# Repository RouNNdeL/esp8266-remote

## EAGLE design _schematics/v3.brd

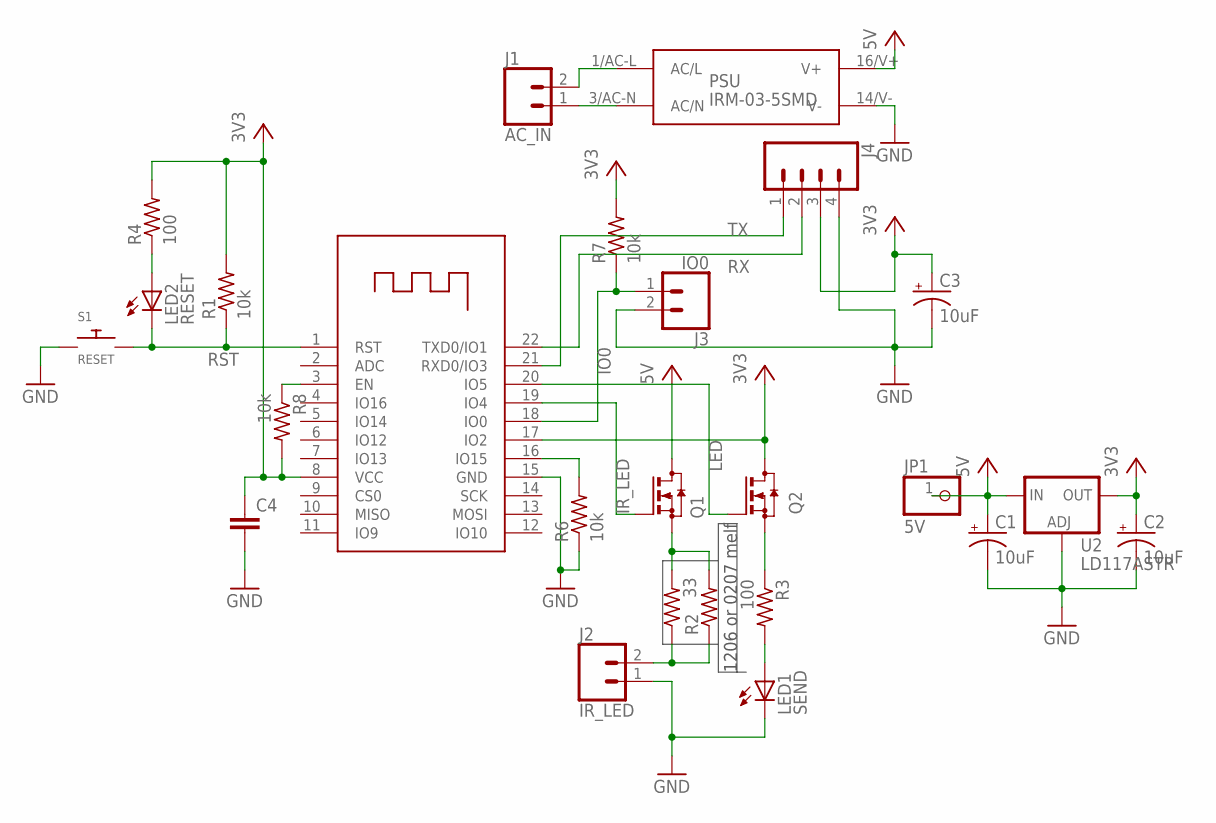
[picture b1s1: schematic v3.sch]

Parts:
C1, C2, C3: 10uF; 153CLV-0405
C4: C-EUC0805; C0805
J1: AC_IN; 1X2_5MM_SCREW
J2: IR_LED; 1X2_5MM_SCREW
J3: IO0; 1X02
J4: CONN_04; 1X04
JP1: 5V; 1X01
LED1: SEND; SML0805
LED2: RESET; SML0805
PSU: IRM-03-5SMD; IRM-03-5S
Q1, Q2: N-MOSFET-SOT23; SOT23
R1, R6, R7, R8: 10k; R0603
R2: 33; MINI_MELF-0207R
R3, R4: 100; R0805
R5: 33; R1206
S1: RESET; B3F-1000
U1: ESP-12F
U2: LD117ASTR; SOT223

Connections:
3V3: C2.+, C3.+, C4.1, J4.3, Q2.3 (D), R1.2, R4.2, R7.2, R8.2, U1.8 (VCC), U1.17 (IO2), U2.4 (OUT)
5V: C1.+, JP1.1, PSU.16/V+ (V+), Q1.3 (D), U2.3 (IN)
AC/L: J1.2, PSU.1/AC-L (AC/L)
AC/N: J1.1, PSU.3/AC-N (AC/N)
EN: R8.1, U1.3 (EN)
GND: C1.-, C2.-, C3.-, C4.2, J2.1, J3.2, J4.4, LED1.C, PSU.14/V- (V-), R6.1, S1.1, S1.2, U1.15 (GND), U2.1 (ADJ)
IO0: J3.1, R7.1, U1.18 (IO0)
IR_LED: Q1.1 (G), U1.19 (IO4)
LED: Q2.1 (G), U1.20 (IO5)
unnamed: LED2.A, R4.1
unnamed: LED1.A, R3.2
unnamed: R6.2, U1.16 (IO15)
unnamed: Q2.2 (S), R3.1
unnamed: Q1.2 (S), R2.2, R5.2
unnamed: J2.2, R2.1, R5.1
RST: LED2.C, R1.1, S1.3, S1.4, U1.1 (RST)
RX: J4.2, U1.22 (TXD0/IO1)
TX: J4.1, U1.21 (RXD0/IO3)

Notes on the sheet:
1206 or 0207 melf

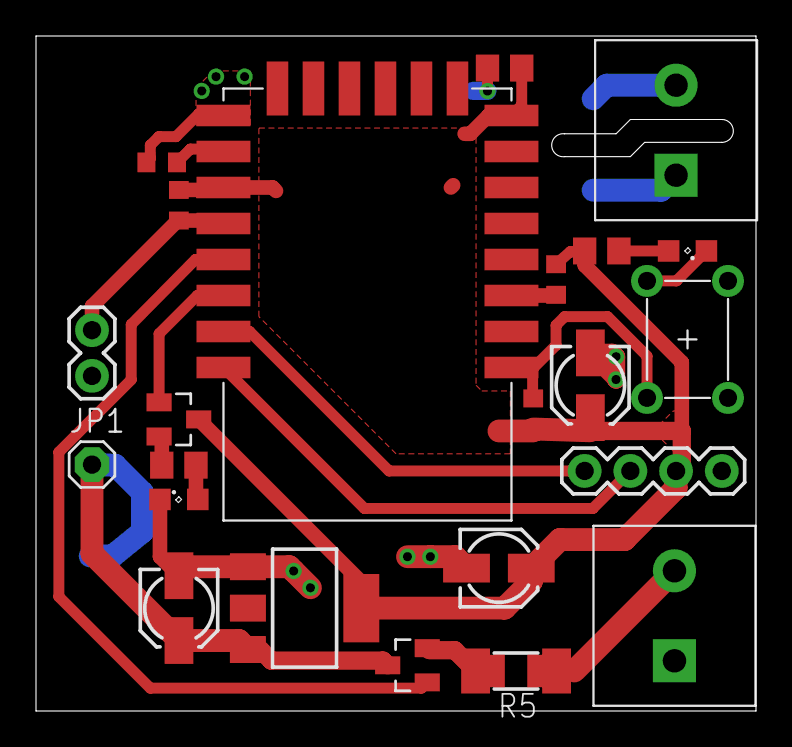
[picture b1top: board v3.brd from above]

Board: 2 copper layers, 40.0 x 37.5 mm, 25 parts (1 on the bottom side), 18 nets.

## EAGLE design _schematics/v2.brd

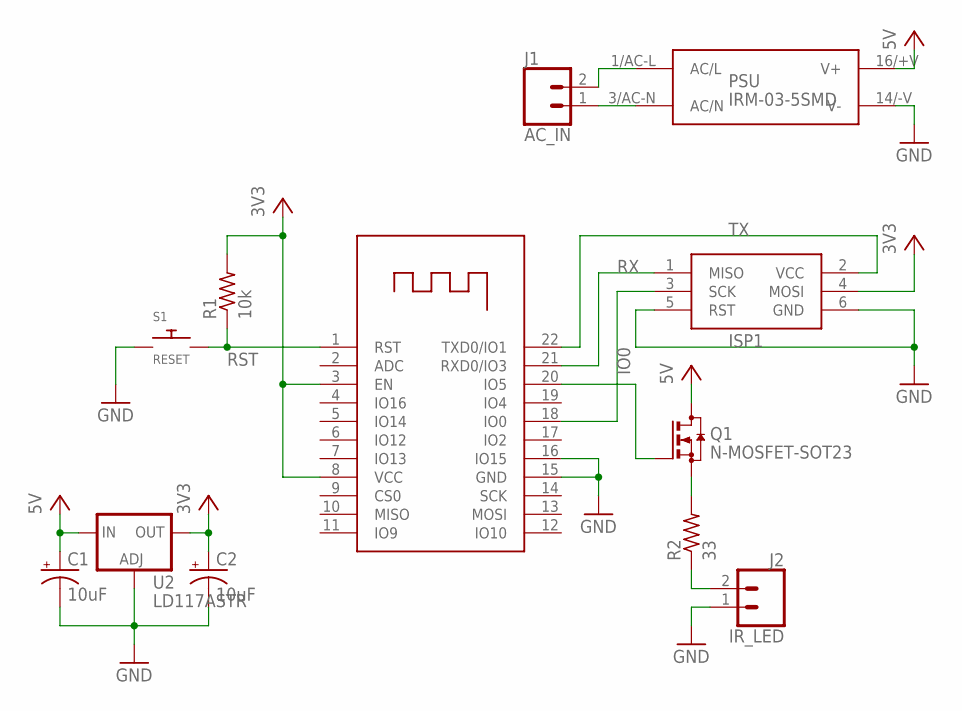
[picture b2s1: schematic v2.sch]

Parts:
C1, C2: 10uF; 153CLV-0405
ISP1: AVRISP-6; AVRISP
J1: AC_IN; 1X2_5MM_SCREW
J2: IR_LED; 1X2_5MM_SCREW
PSU: IRM-03-5SMD; IRM-03-5S
Q1: N-MOSFET-SOT23; SOT23
R1: 10k; R0805
R2: 33; MINI_MELF-0207R
S1: RESET; B3F-1000
U1: ESP-12F
U2: LD117ASTR; SOT223

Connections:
3V3: C2.+, ISP1.4 (MOSI), R1.2, U1.3 (EN), U1.8 (VCC), U2.4 (OUT)
5V: C1.+, PSU.16/+V (V+), Q1.3 (D), U2.3 (IN)
AC/L: J1.2, PSU.1/AC-L (AC/L)
AC/N: J1.1, PSU.3/AC-N (AC/N)
GND: C1.-, C2.-, ISP1.5 (RST), ISP1.6 (GND), J2.1, PSU.14/-V (V-), S1.1, S1.2, U1.15 (GND), U1.16 (IO15), U2.1 (ADJ)
IO0: ISP1.3 (SCK), U1.18 (IO0)
LED: Q1.1 (G), U1.20 (IO5)
unnamed: Q1.2 (S), R2.2
unnamed: J2.2, R2.1
RST: R1.1, S1.3, S1.4, U1.1 (RST)
RX: ISP1.1 (MISO), U1.21 (RXD0/IO3)
TX: ISP1.2 (VCC), U1.22 (TXD0/IO1)

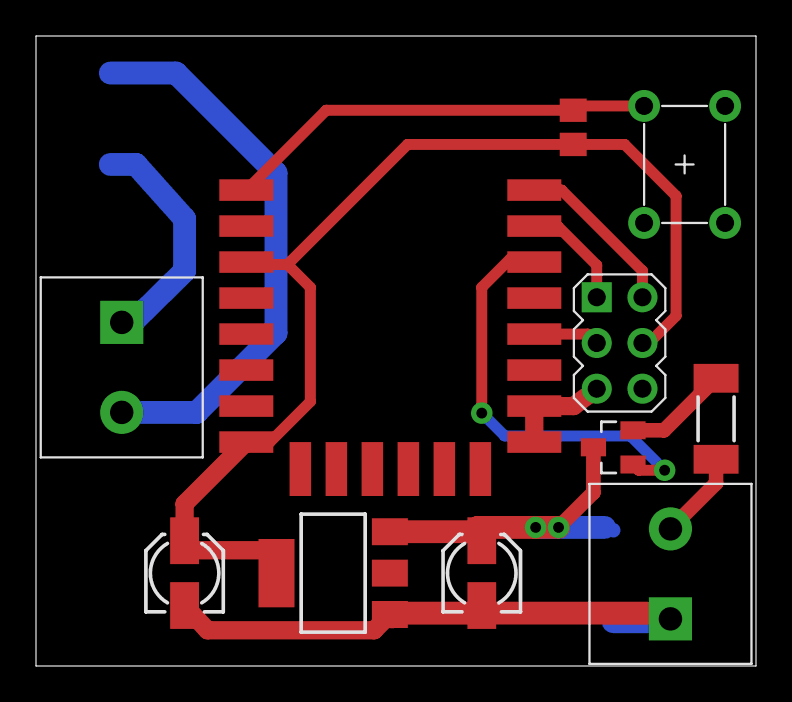
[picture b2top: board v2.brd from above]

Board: 2 copper layers, 40.0 x 35.0 mm, 12 parts (1 on the bottom side), 12 nets.

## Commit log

2018-05-13 Create LICENSE
2018-05-23 Update schematics
2018-07-09 Add NEC and Panasonic codes support
2019-01-17 Overhaul the http endpoint Those changes have not been committed for over 3 months
2019-06-07 Add 36kHz raw code support
2019-06-10 Remove delay when sending Panasonic power codes
2019-06-10 Change raw multiplier to 5

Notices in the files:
_schematics/v2.brd:
© 2018 Krzysztof Zdulski
parts and their libraries:
SparkFun-Connectors: Licensing: Creative Commons ShareAlike 4.0 International - https://creativecommons.org/licenses/by-sa/4.0
